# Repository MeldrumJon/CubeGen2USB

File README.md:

# CubeGen2USB

GameCube and Sega Genesis to USB adapter.  Works for both XInput and DInput 
(depending on which Arduino sketch is used). Only one controller may be used at 
a time (if both controllers are plugged in, the GameCube controller is used).

## Parts

- Arduino Micro
- 1x [DB9 Male Connector](https://www.mouser.com/ProductDetail/571-2301843-1)
- 1x GameCube controller extension cable, cut in half with wires stripped.
- 5x [SPDT Slide Switches](https://www.amazon.com/gp/product/B01M1CU2B0/)
- 1x [Bi-Direction 3.3V-5V Logic Level Converter Module](https://www.amazon.com/gp/product/B07F7W91LC/)
	- or 1x BSS138 MOSFET and 2x 10k resistors.
- Breakaway Headers

Be careful when soldering the GameCube extension cable wires onto the PCB.  Use 
[this](https://github.com/NicoHood/Nintendo/wiki/Gamecube#hardware) as a reference, 
but disregard the wire colors.  Use a continuity tester to determine which wire 
is connected to each pin.

## PCB

KiCAD files are in the [hardware](./hardware) folder.

3rd-party KiCAD libaries used:

- [Arduino KiCAD Library](https://github.com/Alarm-Siren/arduino-kicad-library)

## Programming

### DInput Setup

#### Required Libraries

- [SegaController by Jon Thysell](https://github.com/jonthysell/SegaController)
- Nintendo by NicoHood
- HID-Project by NicoHood

### XInput Setup

#### Hardware Setup

1. Download
[XInput USB Core for Arduino AVR](https://github.com/dmadison/ArduinoXInput_AVR) 
and extract it to `Arduino/hardware/xinput/avr`.
1. Change the board in Arduino IDE to "Arduino Micro w/ XInput".
1. Burn the bootloader using an In-circuit Serial Programmer ([Another Arduino 
can be used as an ISP](https://www.arduino.cc/en/tutorial/arduinoISP)).

Once the bootloader is burned, you will have to press the reset button when 
uploading sketches or simply upload using the ISP.

#### Required Libraries

- [SegaController by Jon Thysell](https://github.com/jonthysell/SegaController)
- Nintendo by NicoHood
- XInput by David Madison

## Features

The five switches can be used to control how buttons are mapped to the emulated 
XBox 360 controller. By default:

| XBox     | GameCube         | Genesis |
| -------- | ---------------- | ------- |
| Start    | Start            | Start   |
| A        | A                | A       |
| B        | B                | B       |
| X        | X                | X       |
| Y        | Y                | Y       |
| L Bumper | L Trigger Button | C       |
| R Bumper | R Trigger Button | Mode    |

- SW1: Swap A&B, X&Y
- SW2: Z maps to R Bumper
- SW3: 
- SW4: 
- SW5:

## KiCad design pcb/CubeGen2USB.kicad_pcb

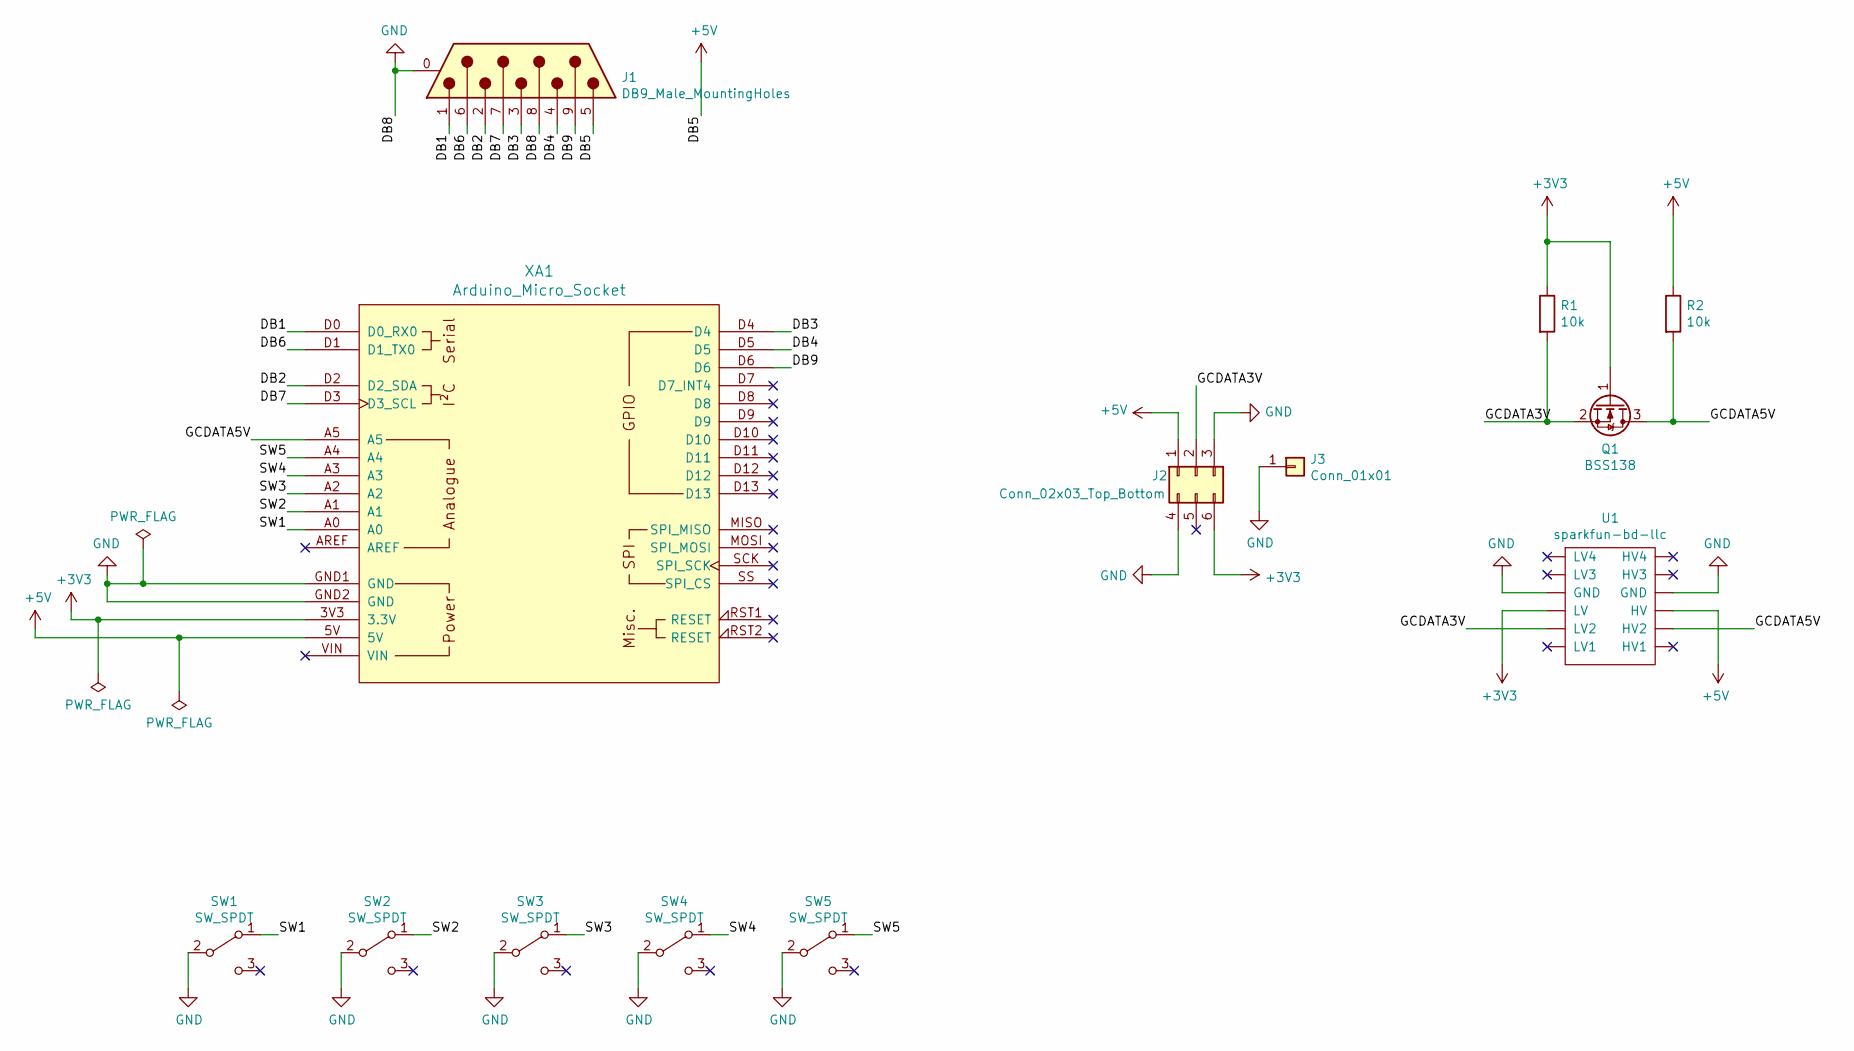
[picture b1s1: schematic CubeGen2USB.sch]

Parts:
J1: DB9_Male_MountingHoles; DB9-2301843-1
J2: Conn_02x03_Top_Bottom; PinSocket_2x03_P2.54mm_Vertical
J3: Conn_01x01; PinSocket_1x01_P2.54mm_Vertical
Q1: BSS138; SOT-23_Handsoldering
R1, R2: 10k; R_Axial_DIN0207_L6.3mm_D2.5mm_P2.54mm_Vertical
SW1, SW2, SW3, SW4, SW5: SW_SPDT; SPDT_THT_Slide_SW
U1: sparkfun-bd-llc
XA1: Arduino_Micro_Socket; Arduino_Micro_Socket_noHoles

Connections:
+3V3: J2.6, Q1.1 (G), R1.1, U1.LV, XA1.3V3 (3.3V)
+5V: J1.5, J2.1, R2.1, U1.HV, XA1.5V
/DB1: J1.1, XA1.D0 (D0_RX0)
/DB2: J1.2, XA1.D2 (D2_SDA)
/DB3: J1.3, XA1.D4
/DB4: J1.4, XA1.D5
/DB6: J1.6, XA1.D1 (D1_TX0)
/DB7: J1.7, XA1.D3 (D3_SCL)
/DB9: J1.9, XA1.D6
/GCDATA3V: J2.2, Q1.2 (S), R1.2, U1.LV2
/GCDATA5V: Q1.3 (D), R2.2, U1.HV2, XA1.A5
/SW1: SW1.1 (A), XA1.A0
/SW2: SW2.1 (A), XA1.A1
/SW3: SW3.1 (A), XA1.A2
/SW4: SW4.1 (A), XA1.A3
/SW5: SW5.1 (A), XA1.A4
GND: J1.0 (PAD), J1.8, J2.3, J2.4, J3.1, SW1.2 (B), SW2.2 (B), SW3.2 (B), SW4.2 (B), SW5.2 (B), U1.GNDH (GND), U1.GNDL (GND), XA1.GND1 (GND), XA1.GND2 (GND)

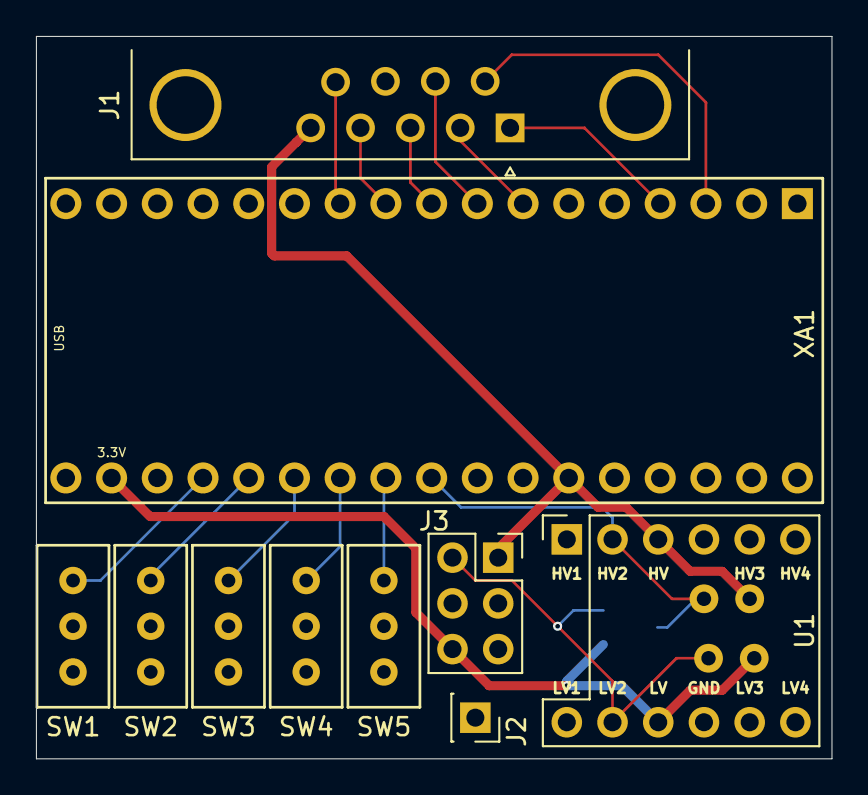
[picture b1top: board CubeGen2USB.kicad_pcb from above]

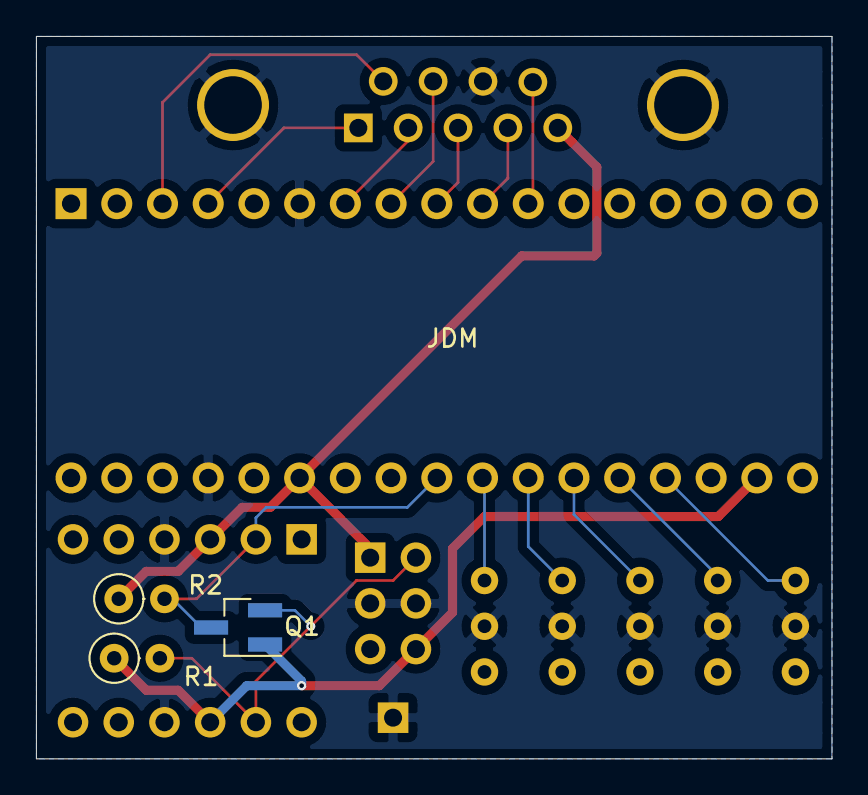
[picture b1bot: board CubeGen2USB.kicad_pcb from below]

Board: 2 copper layers, 44.2 x 40.1 mm, 13 parts (3 on the bottom side), 17 nets.

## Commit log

2019-11-28 PCB, Sketches
2019-11-28 Small silkscreen update
2020-02-03 Working Sketches, README Guide
2020-02-03 Init
2020-02-03 Add Pictures
2020-02-11 Reorganize
2020-02-23 Update Documentation
